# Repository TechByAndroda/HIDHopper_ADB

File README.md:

# HIDHopper ADB

HIDHopper ADB is a modified (forked) version of adbuino and QuokkADB.  It is a Raspberry Pi Pico based hardware device which converts USB keyboard and mouse inputs to the Apple Desktop Bus (ADB) standard.

# The Name
HIDHopper comes from the USB "HID" standard, for Human Interface Device.  Hopper just sounded right after HID.

# Picture

# Usage
See the file [doc/HIDHopper.md](https://github.com/TechByAndroda/HIDHopper_ADB/blob/master/doc/HIDHopper.md) for more full documentation

# Quick Usage
- For Base HIDHopper without USB Hub, *before* turning on your computer:
   - Plug in your desired USB peripheral (keyboard or mouse)
   - Plug HIDHopper into the ADB bus
   - Start computer
   - Hot-plug *is not supported*, don't unplug from the ADB Bus *or* unplug the USB device that is connected while the computer is on
- For HIDHopper with the USB Hub Hat, *before* turning on your computer:
   - Ensure the Hub is solidly secured in place with the two mounting screws and top cover plate
   - Plug HIDHopper into the ADB bus
   - Plug in your external 5v USB-C power supply to the connector on the Hub
      - You *must use USB-C External Power* to avoid blowing the ADB Power fuse on your motherboard!
   - Plug in your desired USB keyboard and mouse
   - Hot-plug *is not supported*, don't unplug from the ADB Bus *or* unplug USB devices that are connected while the computer is on
      - Hot-plug of USB devices is finicky, sometimes it works and other times it does not
      - Best to connect before startup, that always works

# Background

This is a fork of Difegue's version of the [adbuino](https://github.com/Difegue/Chaotic-Realm), which was a modified version of [bbraun's](http://synack.net/svn/adbduino/) PS/2 to ADB arduino sketch, with some extra code added to alleviate issues with his own PS/2 keyboard.  For Difegue's original write-up, please read more info [here.](https://tvc-16.science/adbuino-ps2.html).

# How to build and flash HIDHopper ADB

Note: This software is intended to be compiled in an Ubuntu Linux environment.

- Install the Raspberry Pi Pico SDK (https://github.com/raspberrypi/pico-sdk)
- Set the `$PICO_SDK_PATH` environment variable to your pico-sdk directory
- Open a Terminal and "cd" into this project
- From the top level of this project, "cd" to the `src/firmware` folder
- In Terminal, execute the following commands from the above `src/firmware` folder:
  - `mkdir build`
  - `cd build`
  - `cmake ..`
  - `make`
- The build outputs (.uf2, .bin, .elf, etc) will be placed in this folder (path is from the top level of the project):
  - `src/firmware/build/src`
- Next, plug the micro-USB side of a USB cable into HIDHopper
- Press the button which is near the micro-USB port
- While holding down the button, plug the USB cable into your computer (then release the button after plugging in)
- You should see an "RPI-RP2" mass storage device appear on your computer
- Drag the ".uf2" file onto that mass storage device
- Once the mass storage device disappears, wait 10 seconds and then you are free to unplug

# References

## Protocol/Software Documentation
- [Apple ADB Manager Documenation](https://developer.apple.com/library/archive/documentation/mac/pdf/Devices/ADB_Manager.pdf)
- [ADB Overview](https://www.lopaciuk.eu/2021/03/26/apple-adb-protocol.html)
- [Microchip Application Note AN591](http://www.t-es-t.hu/download/microchip/an591b.pdf)
- [TMK Documentation](https://github.com/tmk/tmk_keyboard/wiki/Apple-Desktop-Bus)

## Other libraries
- [TinyUSB Library](https://github.com/raspberrypi/tinyusb)
- [MiSTER adb hardware emulation](https://github.com/mist-devel/plus_too/blob/master/adb.v)

## Development resources
- [Running OpenOCD without root](https://forgge.github.io/theCore/guides/running-openocd-without-sudo.html)

## Hardware Links
- [ADB Connector - mouser](https://www.mouser.com/ProductDetail/TE-Connectivity/5749181-1?qs=XlZqES4cpWbRcAMR%2FcJqkQ%3D%3D)

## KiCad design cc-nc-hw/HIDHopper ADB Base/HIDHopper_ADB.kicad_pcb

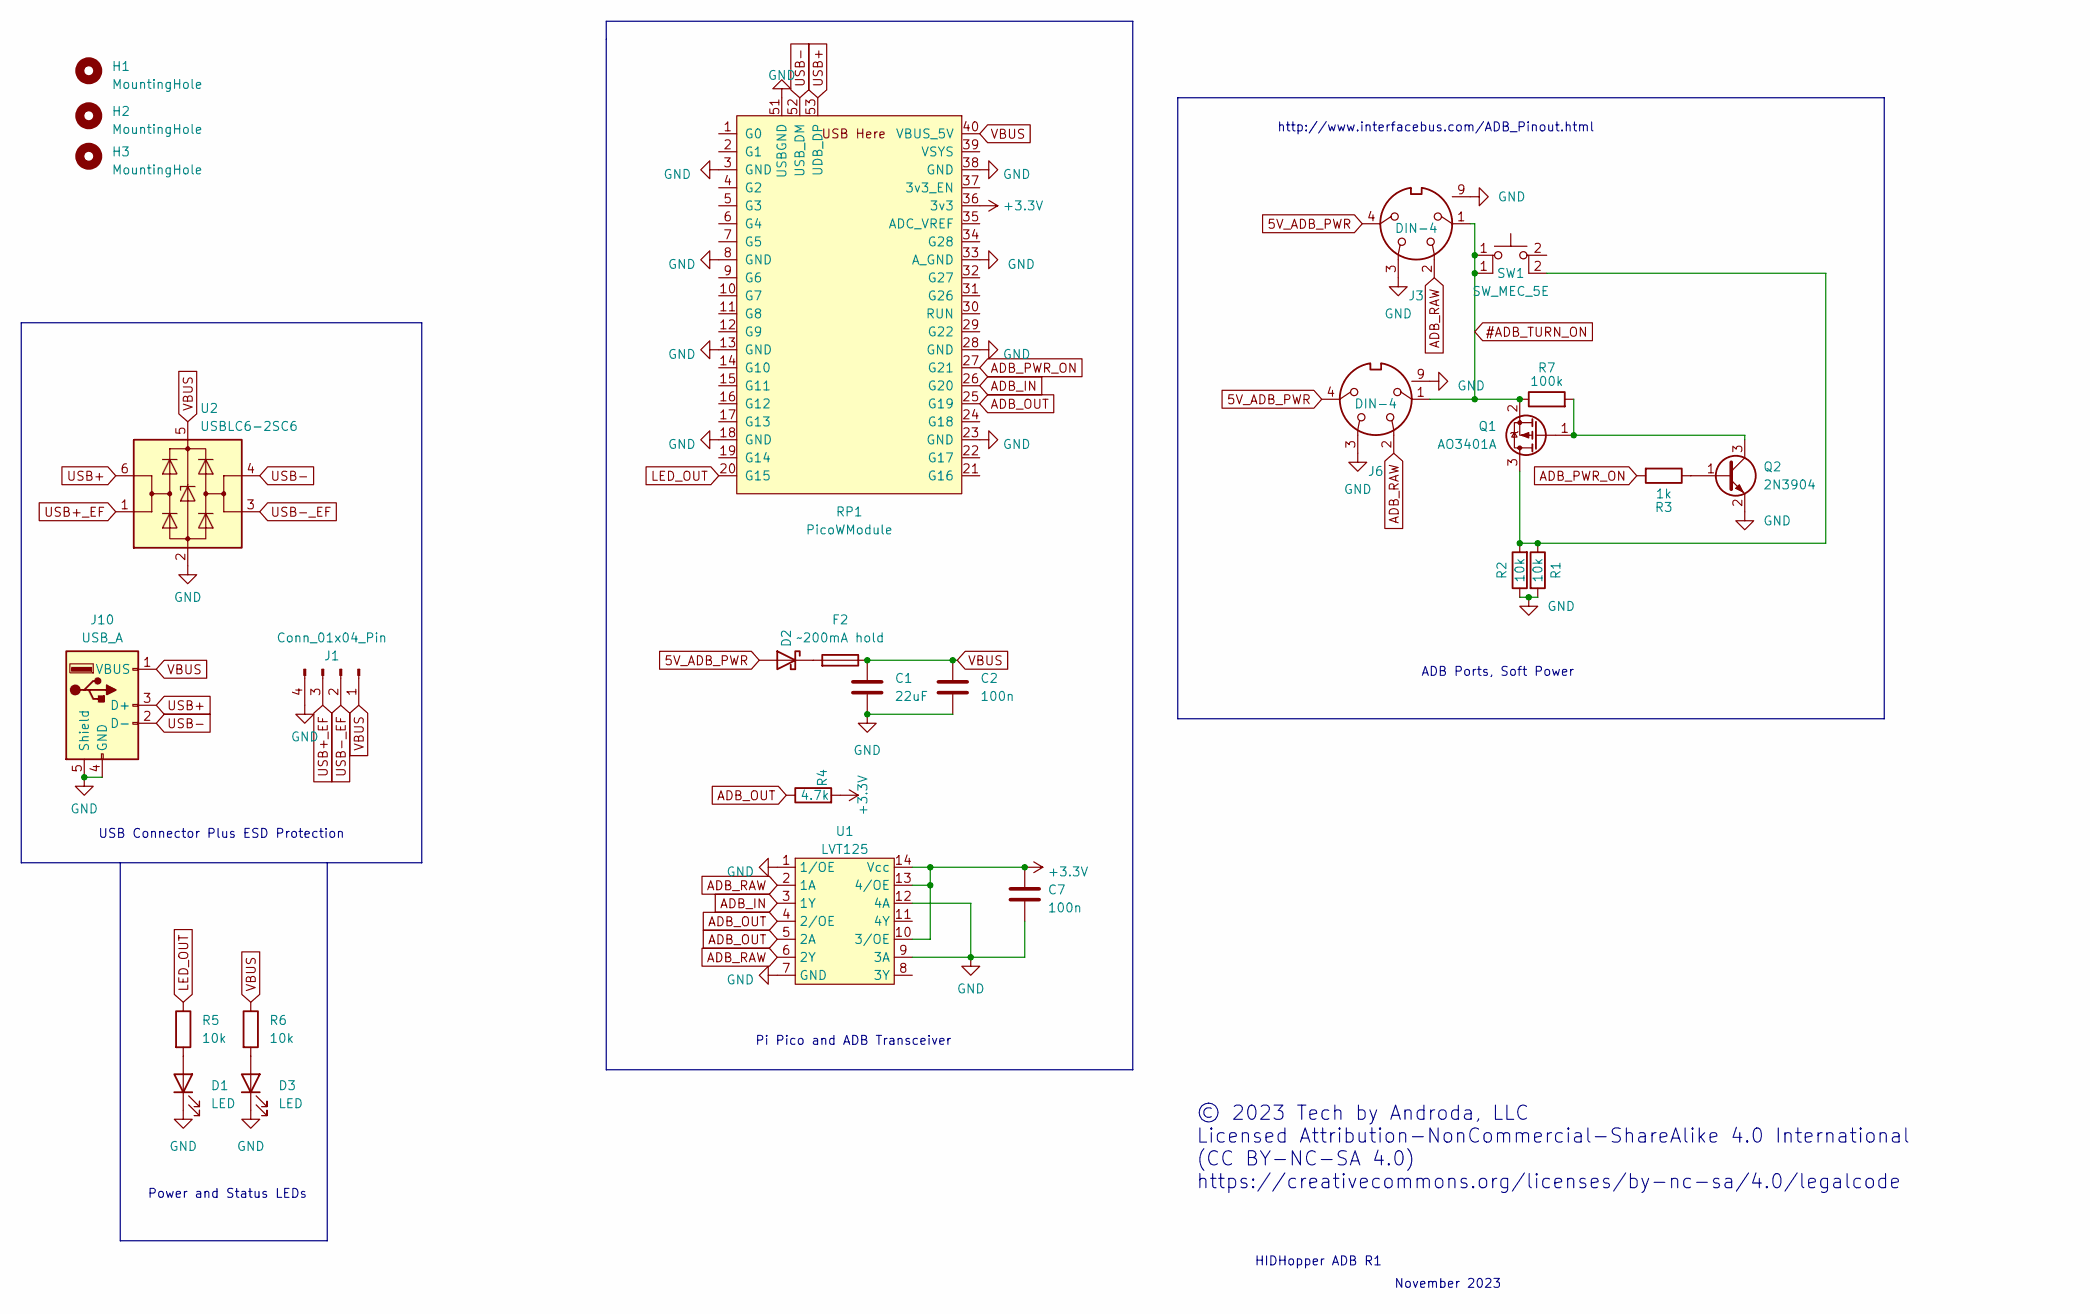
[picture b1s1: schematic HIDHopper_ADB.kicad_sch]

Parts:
C1: 22uF; C_1206_3216Metric
C2, C7: 100n; C_0805_2012Metric
D1, D3: LED; LED_0805_2012Metric
D2: D_Schottky; D_SMA
F2: ~200mA hold; Fuse_0603_1608Metric
H1, H2, H3: MountingHole; MountingHole_3.2mm_M3
J1: Conn_01x04_Pin; PinHeader_1x04_P2.54mm_Vertical
J3, J6: DIN-4; ADB_MDR4_MINI-DIN
J10: USB_A; USB_A_Molex_67643_Horizontal
Q1: AO3401A; SOT-23
Q2: 2N3904; SOT-23
R1, R2, R5, R6: 10k; R_0603_1608Metric
R3: 1k; R_0603_1608Metric
R4: 4.7k; R_0603_1608Metric
R7: 100k; R_0603_1608Metric
RP1: PicoWModule; Raspberry_Pi_PicoW_SMT_THT
SW1: SW_MEC_5E; TS-1187A-B-A-B
U1: LVT125; TSSOP-14_4.4x5mm_P0.65mm
U2: USBLC6-2SC6; SOT-23-6

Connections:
5V_ADB_PWR: D2.2 (A), J3.4, J6.4
#ADB_TURN_ON: J3.1, J6.1, Q1.2 (S), R7.1, SW1.1
+3.3V: C7.1, R4.2, RP1.36 (3v3), U1.10 (3/OE), U1.13 (4/OE), U1.14 (Vcc)
ADB_IN: RP1.26 (G20), U1.3 (1Y)
ADB_OUT: R4.1, RP1.25 (G19), U1.4 (2/OE), U1.5 (2A)
ADB_PWR_ON: R3.2, RP1.27 (G21)
ADB_RAW: J3.2, J6.2, U1.2 (1A), U1.6 (2Y)
GND: C1.2, C2.2, C7.2, D1.1 (K), D3.1 (K), J1.4, J3.3, J3.9, J6.3, J6.9, J10.4 (GND), J10.5 (Shield), Q2.2 (E), R1.2, R2.1, RP1.3 (GND), RP1.8 (GND), RP1.13 (GND), RP1.18 (GND), RP1.23 (GND), RP1.28 (GND), RP1.33 (A_GND), RP1.38 (GND), RP1.51 (USBGND), U1.1 (1/OE), U1.7 (GND), U1.9 (3A), U1.12 (4A), U2.2 (GND)
LED_OUT: R5.1, RP1.20 (G15)
unnamed: D1.2 (A), R5.2
unnamed: D2.1 (K), F2.2
unnamed: D3.2 (A), R6.2
unnamed: Q1.3 (D), R1.1, R2.2, SW1.2
unnamed: Q1.1 (G), Q2.3 (C), R7.2
unnamed: Q2.1 (B), R3.1
USB+: J10.3 (D+), RP1.53 (UDB_DP), U2.6 (I/O1)
USB+_EF: J1.3, U2.1 (I/O1)
USB-: J10.2 (D-), RP1.52 (USB_DM), U2.4 (I/O2)
USB-_EF: J1.2, U2.3 (I/O2)
VBUS: C1.1, C2.1, F2.1, J1.1, J10.1 (VBUS), R6.1, RP1.40 (VBUS_5V), U2.5 (VBUS)

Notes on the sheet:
Pi Pico and ADB Transceiver
HIDHopper ADB R1
ADB Ports, Soft Power
© 2023 Tech by Androda, LLC Licensed Attribution-NonCommercial-ShareAlike 4.0 International (CC BY-NC-SA 4.0) https://creativecommons.org/licenses/by-nc-sa/4.0/legalcode
November 2023
USB Connector Plus ESD Protection
http://www.interfacebus.com/ADB_Pinout.html
Power and Status LEDs

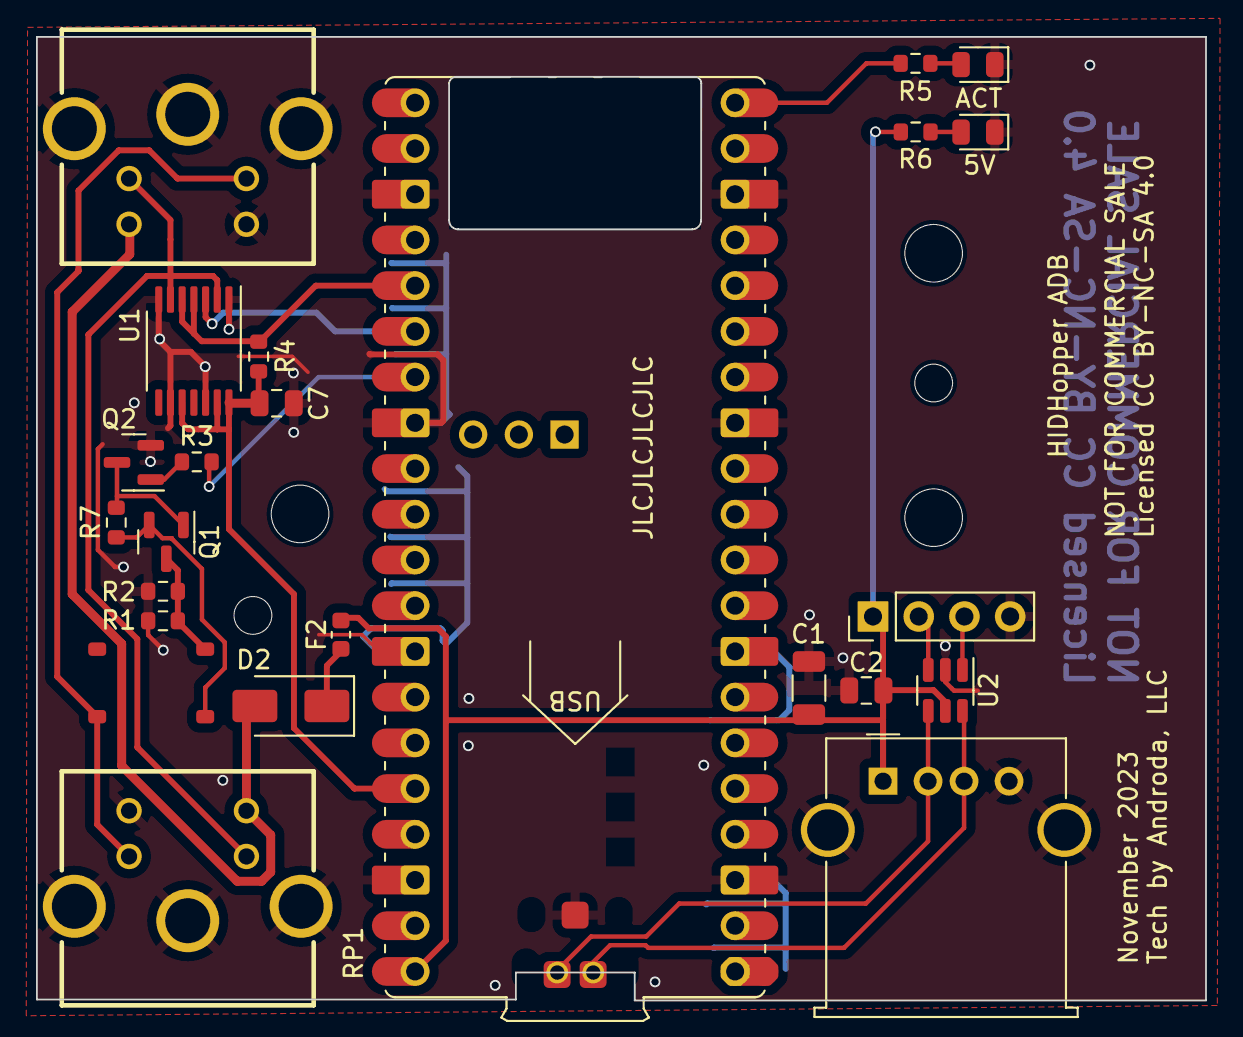
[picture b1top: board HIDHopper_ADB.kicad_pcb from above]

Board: 2 copper layers, 64.9 x 53.5 mm, 27 parts (0 on the bottom side), 20 nets.

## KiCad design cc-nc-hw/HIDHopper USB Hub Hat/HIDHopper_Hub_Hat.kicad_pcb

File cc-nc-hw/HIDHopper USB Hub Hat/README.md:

# HIDHopper ADB (and USB Hub Hat) PCB Design and Production Files

All files here, in and under the cc-nc-hw folder, are provided under the [Attribution-NonCommercial-ShareAlike 4.0 International License](https://creativecommons.org/licenses/by-nc-sa/4.0/deed.en)

This license was selected with the intent to allow you to produce these for personal use only, not for sale.
Please do not produce a run of these and ask to "sell the extras", those sales are in violation of the license.

Please obey the terms of this license in your usage of these files.
Any product listings for these CC-NC licensed versions will receive a notice of license infringement with expectation that the listings are taken down.

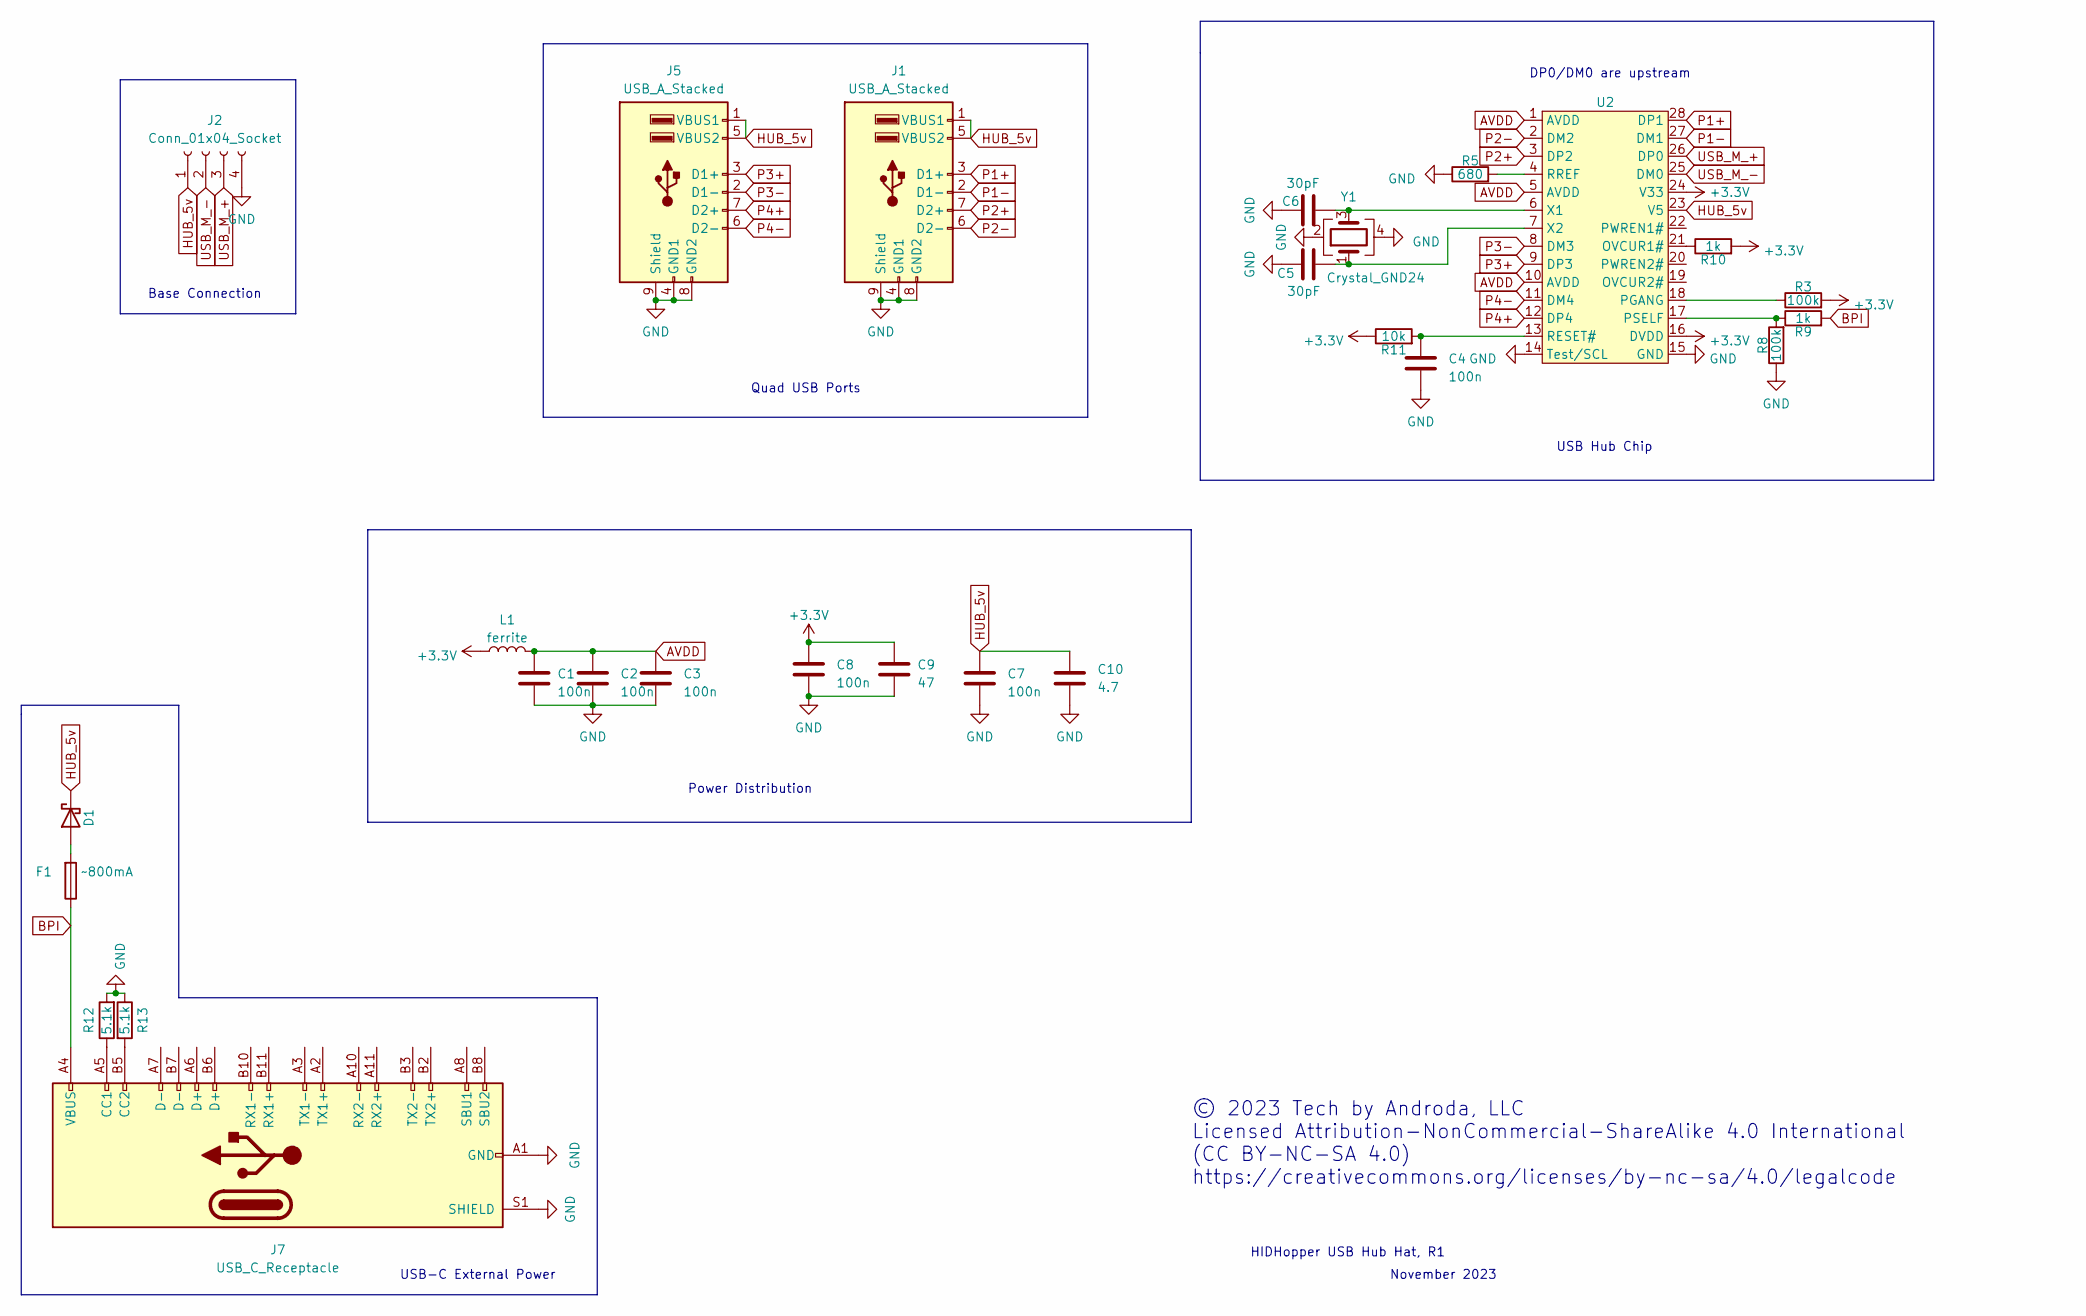
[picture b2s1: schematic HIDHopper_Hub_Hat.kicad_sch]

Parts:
C1, C2, C3, C7, C8: 100n; C_0805_2012Metric
C4: 100n
C5, C6: 30pF; C_0402_1005Metric
C9: 47; C_1206_3216Metric
C10: 4.7; C_0805_2012Metric
D1: D_Schottky; D_SMA
F1: ~800mA; Fuse_0805_2012Metric
J1, J5: USB_A_Stacked; USB_A_CUI_UJ2-ADH-TH_Horizontal_Stacked
J2: Conn_01x04_Socket; PinSocket_1x04_P2.54mm_Vertical
J7: USB_C_Receptacle; USB_C_Receptacle_HRO_TYPE-C-31-M-12
L1: ferrite; L_0805_2012Metric
R3, R8: 100k; R_0603_1608Metric
R5: 680; R_0603_1608Metric
R9, R10: 1k; R_0603_1608Metric
R11: 10k
R12, R13: 5.1k; R_0402_1005Metric
U2: SSOP-28_5.3x10.2mm_P0.65mm
Y1: Crystal_GND24; Crystal_SMD_3225-4Pin_3.2x2.5mm

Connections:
+3.3V: C8.1, C9.1, L1.1, R3.2, R10.2, R11.1, U2.16 (DVDD), U2.24 (V33)
AVDD: C1.1, C2.1, C3.1, L1.2, U2.1 (AVDD), U2.5 (AVDD), U2.10 (AVDD)
BPI: F1.1, J7.A4 (VBUS), J7.A9 (VBUS), J7.B4 (VBUS), J7.B9 (VBUS), R9.2
GND: C1.2, C2.2, C3.2, C4.2, C5.2, C6.2, C7.2, C8.2, C9.2, C10.2, J1.4 (GND1), J1.8 (GND2), J1.9 (Shield), J2.4, J5.4 (GND1), J5.8 (GND2), J5.9 (Shield), J7.A1 (GND), J7.A12 (GND), J7.B1 (GND), J7.B12 (GND), J7.S1 (SHIELD), R5.1, R8.1, R12.2, R13.1, U2.14 (Test/SCL), U2.15 (GND), Y1.2, Y1.4
HUB_5v: C7.1, C10.1, D1.1 (K), J1.1 (VBUS1), J1.5 (VBUS2), J2.1, J5.1 (VBUS1), J5.5 (VBUS2), U2.23 (V5)
unnamed: D1.2 (A), F1.2
unnamed: J7.A5 (CC1), R12.1
unnamed: J7.B5 (CC2), R13.2
unnamed: R10.1, U2.21 (OVCUR1#)
unnamed: R3.1, U2.18 (PGANG)
unnamed: R8.2, R9.1, U2.17 (PSELF)
unnamed: C4.1, R11.2, U2.13 (RESET#)
unnamed: R5.2, U2.4 (RREF)
unnamed: C6.1, U2.6 (X1), Y1.3
unnamed: C5.1, U2.7 (X2), Y1.1
P1+: J1.3 (D1+), U2.28 (DP1)
P1-: J1.2 (D1-), U2.27 (DM1)
P2+: J1.7 (D2+), U2.3 (DP2)
P2-: J1.6 (D2-), U2.2 (DM2)
P3+: J5.3 (D1+), U2.9 (DP3)
P3-: J5.2 (D1-), U2.8 (DM3)
P4+: J5.7 (D2+), U2.12 (DP4)
P4-: J5.6 (D2-), U2.11 (DM4)
USB_M_+: J2.3, U2.26 (DP0)
USB_M_-: J2.2, U2.25 (DM0)

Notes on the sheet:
HIDHopper USB Hub Hat, R1
USB Hub Chip
November 2023
Power Distribution
Base Connection
© 2023 Tech by Androda, LLC Licensed Attribution-NonCommercial-ShareAlike 4.0 International (CC BY-NC-SA 4.0) https://creativecommons.org/licenses/by-nc-sa/4.0/legalcode
DP0/DM0 are upstream
Quad USB Ports
USB-C External Power

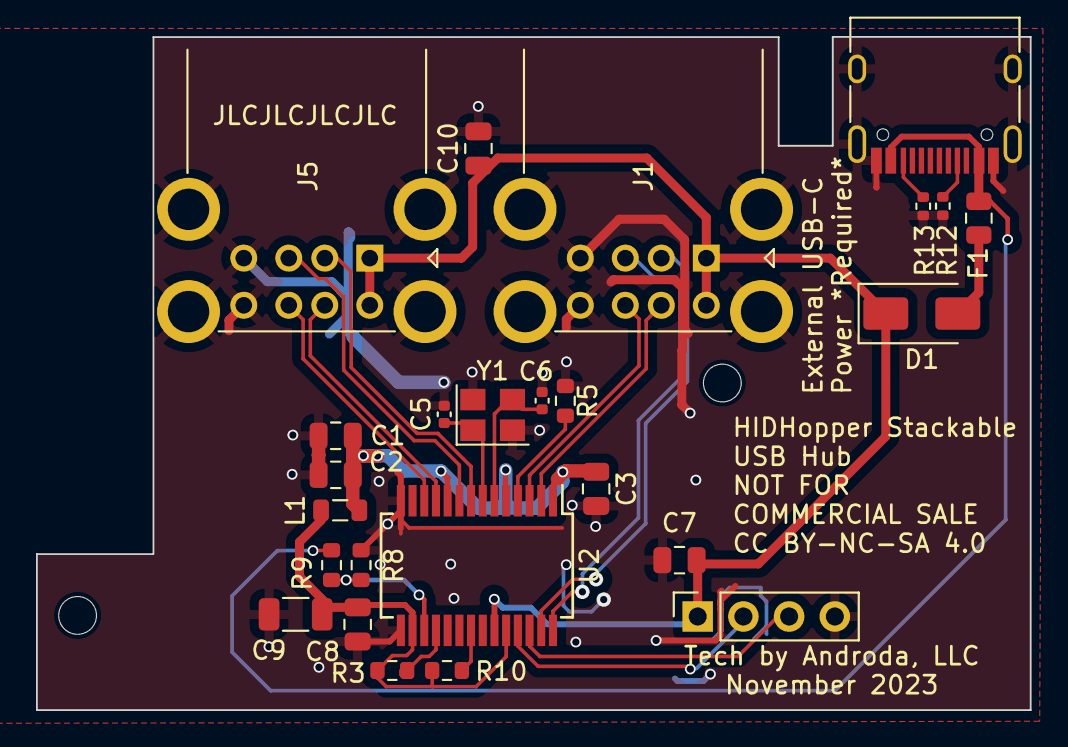
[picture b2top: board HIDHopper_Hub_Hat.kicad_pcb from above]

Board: 2 copper layers, 55.2 x 37.4 mm, 25 parts (0 on the bottom side), 24 nets.

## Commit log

2023-12-28 Add HIDHopper header
2023-12-28 Rebrand binary
2023-12-28 Docs
2024-01-01 Add Pictures
2024-01-01 Update README.md
    Link and image
2024-01-01 Update HIDHopper.md
    Formatting, and pictures
2024-01-01 Another Picture
2024-01-01 Update HIDHopper.md
    Buttons image
2024-01-02 Update README.md
    Explain the name
2024-01-03 Update README.md
    Better Quick Usage
2024-01-03 Update HIDHopper.md
    Compatibility testing and Hub notes
2024-01-06 Updated Case Design Images
2024-01-11 Remove old hw folder, new to be added
2024-01-13 HIDHopper Base and USB Hub Hat, R1
2024-01-18 Update README.md
    Case design was changed, update readme to match
2024-10-23 fix build

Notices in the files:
cc-nc-hw/HIDHopper ADB Base/HIDHopper_ADB.kicad_pcb:
Licensed CC BY-NC-SA 4.0
parts and their libraries:
This public domain footprint does not match the original source as it has been modified to better fit this application
Public Domain As Per:
